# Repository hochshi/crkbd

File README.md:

# Corne keyboard

The Corne Choc-mini keyboard is a split keyboard with 3x5 column staggered keys
and 3 thumb keys, based on [Corne](https://github.com/foostan/crkbd). The inspiration came from David Barr's [Choc-Spaced-Corne](https://github.com/davidphilipbarr/Choc-Spaced-Corne).

## Lineup
- corne-light: 
  Light-weight Corne for choc-mini switches with choc spacing (Easy build with a simple PCB).
- corne-light-track-point: 
  Light-weight Corne for choc-mini switches with choc spacing and a trackpoint under the right thumb (or far-index) (Not ready yet).

### Future Plans
The next iteration will replace one of the micro-controllers with an IO expander

## Photos

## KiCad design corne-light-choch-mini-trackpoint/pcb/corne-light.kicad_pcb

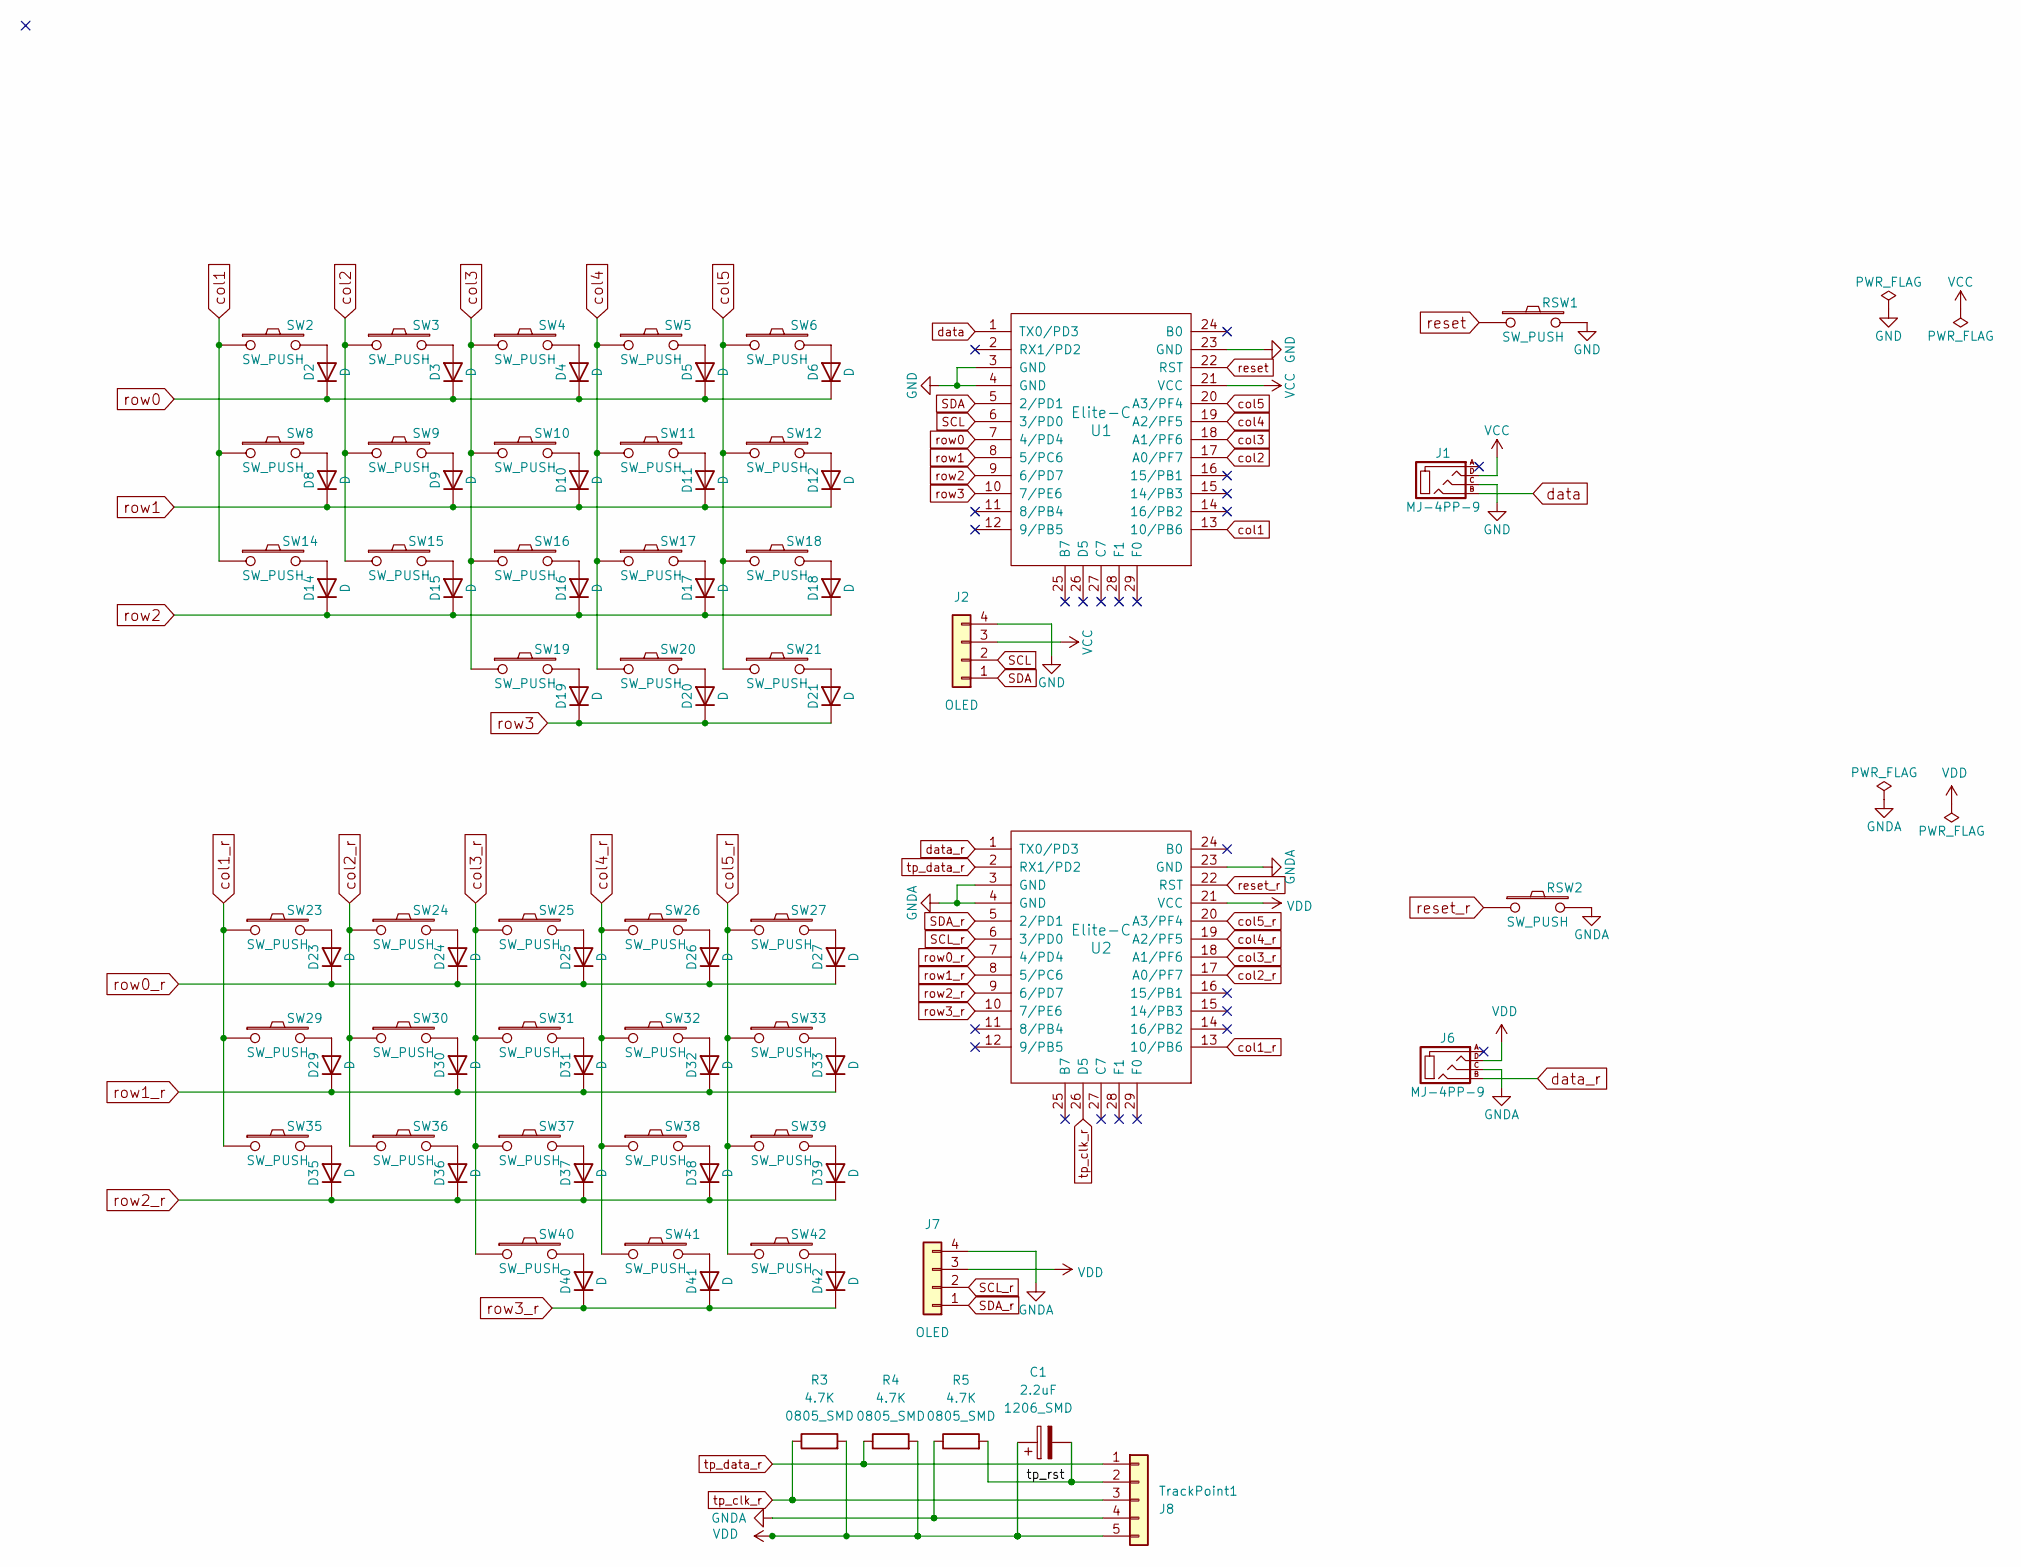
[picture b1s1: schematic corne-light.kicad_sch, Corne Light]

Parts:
C1: 2.2uF; C_1206_3216Metric
D2, D3, D4, D5, D6, D8, D9, D10, D11, D12, D14, D15, D16, D17, D18, D19, D20, D21, D23, D24, D25, D26, D27, D29, D30, D31, D32, D33, D35, D36, D37, D38, D39, D40, D41, D42: D; D3_TH
J1, J6: MJ-4PP-9; MJ-4PP-9_1side
J2, J7: OLED; OLED_1side
R3, R4, R5: 4.7K; R_0805_2012Metric
RSW1, RSW2: SW_PUSH; ResetSW_1side
SW2, SW3, SW4, SW5, SW6, SW8, SW9, SW10, SW11, SW12, SW14, SW15, SW16, SW17, SW18, SW19, SW20, SW21, SW23, SW24, SW25, SW26, SW27, SW29, SW30, SW31, SW32, SW33, SW35, SW36, SW37, SW38, SW39, SW40, SW41, SW42: SW_PUSH; Kailh_PG1232
TrackPoint1: J8; PinHeader_1x05_P2.54mm_Vertical
U1, U2: Elite-C

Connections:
/tp_rst: C1.2, R5.2, TrackPoint1.2; also elsewhere on the board
GND: J1.C, J2.4, RSW1.2, U1.3 (GND), U1.4 (GND), U1.23 (GND)
GNDA: J6.C, J7.4, R5.1, RSW2.2, TrackPoint1.4, U2.3 (GND), U2.4 (GND), U2.23 (GND); also elsewhere on the board
unnamed: D2.2 (A), SW2.2
unnamed: D3.2 (A), SW3.2
unnamed: D4.2 (A), SW4.2
unnamed: D5.2 (A), SW5.2
unnamed: D6.2 (A), SW6.2
unnamed: D8.2 (A), SW8.2
unnamed: D9.2 (A), SW9.2
unnamed: D10.2 (A), SW10.2
unnamed: D11.2 (A), SW11.2
unnamed: D12.2 (A), SW12.2
unnamed: D14.2 (A), SW14.2
unnamed: D15.2 (A), SW15.2
unnamed: D16.2 (A), SW16.2
unnamed: D17.2 (A), SW17.2
unnamed: D18.2 (A), SW18.2
unnamed: D19.2 (A), SW19.2
unnamed: D20.2 (A), SW20.2
unnamed: D21.2 (A), SW21.2
unnamed: D23.2 (A), SW23.2
unnamed: D24.2 (A), SW24.2
unnamed: D25.2 (A), SW25.2
unnamed: D26.2 (A), SW26.2
unnamed: D27.2 (A), SW27.2
unnamed: D29.2 (A), SW29.2
unnamed: D30.2 (A), SW30.2
unnamed: D31.2 (A), SW31.2
unnamed: D32.2 (A), SW32.2
unnamed: D33.2 (A), SW33.2
unnamed: D35.2 (A), SW35.2
unnamed: D36.2 (A), SW36.2
unnamed: D37.2 (A), SW37.2
unnamed: D38.2 (A), SW38.2
unnamed: D39.2 (A), SW39.2
unnamed: D40.2 (A), SW40.2
unnamed: D41.2 (A), SW41.2
unnamed: D42.2 (A), SW42.2
SCL: J2.2, U1.6 (3/PD0)
SCL_r: J7.2, U2.6 (3/PD0)
SDA: J2.1, U1.5 (2/PD1)
SDA_r: J7.1, U2.5 (2/PD1)
VCC: J1.D, J2.3, U1.21 (VCC)
VDD: C1.1, J6.D, J7.3, R3.2, R4.2, TrackPoint1.5, U2.21 (VCC); also elsewhere on the board
col1: SW2.1, SW8.1, SW14.1, U1.13 (10/PB6)
col1_r: SW23.1, SW29.1, SW35.1, U2.13 (10/PB6)
col2: SW3.1, SW9.1, SW15.1, U1.17 (A0/PF7)
col2_r: SW24.1, SW30.1, SW36.1, U2.17 (A0/PF7)
col3: SW4.1, SW10.1, SW16.1, SW19.1, U1.18 (A1/PF6)
col3_r: SW25.1, SW31.1, SW37.1, SW40.1, U2.18 (A1/PF6)
col4: SW5.1, SW11.1, SW17.1, SW20.1, U1.19 (A2/PF5)
col4_r: SW26.1, SW32.1, SW38.1, SW41.1, U2.19 (A2/PF5)
col5: SW6.1, SW12.1, SW18.1, SW21.1, U1.20 (A3/PF4)
col5_r: SW27.1, SW33.1, SW39.1, SW42.1, U2.20 (A3/PF4)
data: J1.B, U1.1 (TX0/PD3)
data_r: J6.B, U2.1 (TX0/PD3)
reset: RSW1.1, U1.22 (RST)
reset_r: RSW2.1, U2.22 (RST)
row0: D2.1 (K), D3.1 (K), D4.1 (K), D5.1 (K), D6.1 (K), U1.7 (4/PD4)
row0_r: D23.1 (K), D24.1 (K), D25.1 (K), D26.1 (K), D27.1 (K), U2.7 (4/PD4)
row1: D8.1 (K), D9.1 (K), D10.1 (K), D11.1 (K), D12.1 (K), U1.8 (5/PC6)
row1_r: D29.1 (K), D30.1 (K), D31.1 (K), D32.1 (K), D33.1 (K), U2.8 (5/PC6)
row2: D14.1 (K), D15.1 (K), D16.1 (K), D17.1 (K), D18.1 (K), U1.9 (6/PD7)
row2_r: D35.1 (K), D36.1 (K), D37.1 (K), D38.1 (K), D39.1 (K), U2.9 (6/PD7)
row3: D19.1 (K), D20.1 (K), D21.1 (K), U1.10 (7/PE6)
row3_r: D40.1 (K), D41.1 (K), D42.1 (K), U2.10 (7/PE6)
tp_clk_r: R3.1, TrackPoint1.3, U2.26 (D5); also elsewhere on the board
tp_data_r: R4.1, TrackPoint1.1, U2.2 (RX1/PD2); also elsewhere on the board

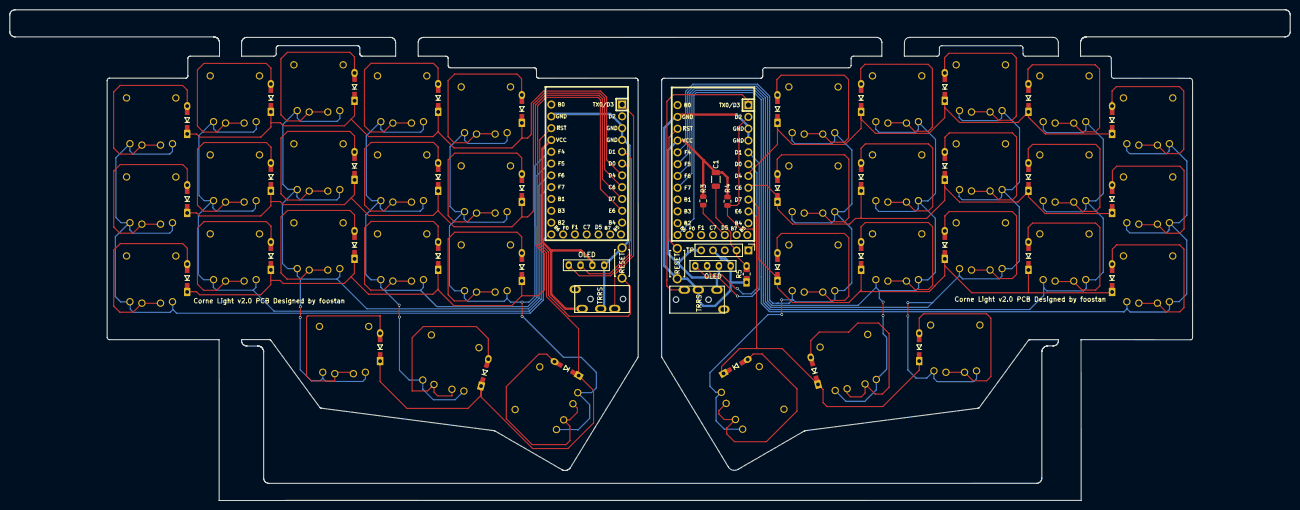
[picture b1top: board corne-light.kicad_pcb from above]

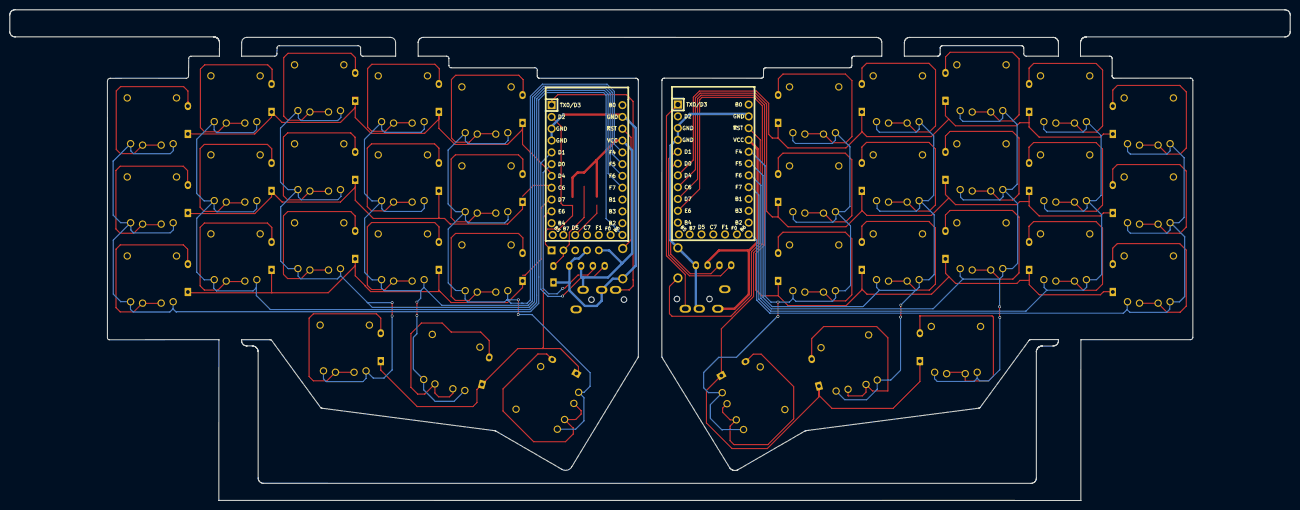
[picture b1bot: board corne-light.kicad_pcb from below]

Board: 2 copper layers, 275.5 x 105.6 mm, 85 parts (2 on the bottom side), 69 nets.

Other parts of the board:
TP: J8; PinHeader_1x05_P2.54mm_Vertical

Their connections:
/tp_rst: TP.2; also elsewhere on the board
GNDA: TP.4; also elsewhere on the board
VDD: TP.5; also elsewhere on the board
tp_clk_r: TP.3; also elsewhere on the board
tp_data_r: TP.1; also elsewhere on the board

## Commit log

2022-12-12 Added track pad support with reset board soldered on the pcb
2023-01-04 Added corne-light choc-mini trackpoint
2023-01-04 Fixed typo in dir names
2023-01-04 Added keebio's component and footprints
2023-01-04 Moved submodules to the proper location
